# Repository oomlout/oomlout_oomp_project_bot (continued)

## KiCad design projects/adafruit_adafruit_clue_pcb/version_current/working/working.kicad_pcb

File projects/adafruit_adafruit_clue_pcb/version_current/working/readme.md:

# Adafruit-CLUE-PCB by adafruit  
This is a harvested standardized copy of a project from github.  
The original project can be found at:  
https://github.com/adafruit/Adafruit-CLUE-PCB  
Please consult that link for additional, details, files, and license information.  
Note: It was auto harvested and if the original repo had more than one board file or anything out of the ordinary the files here are likely not representative.

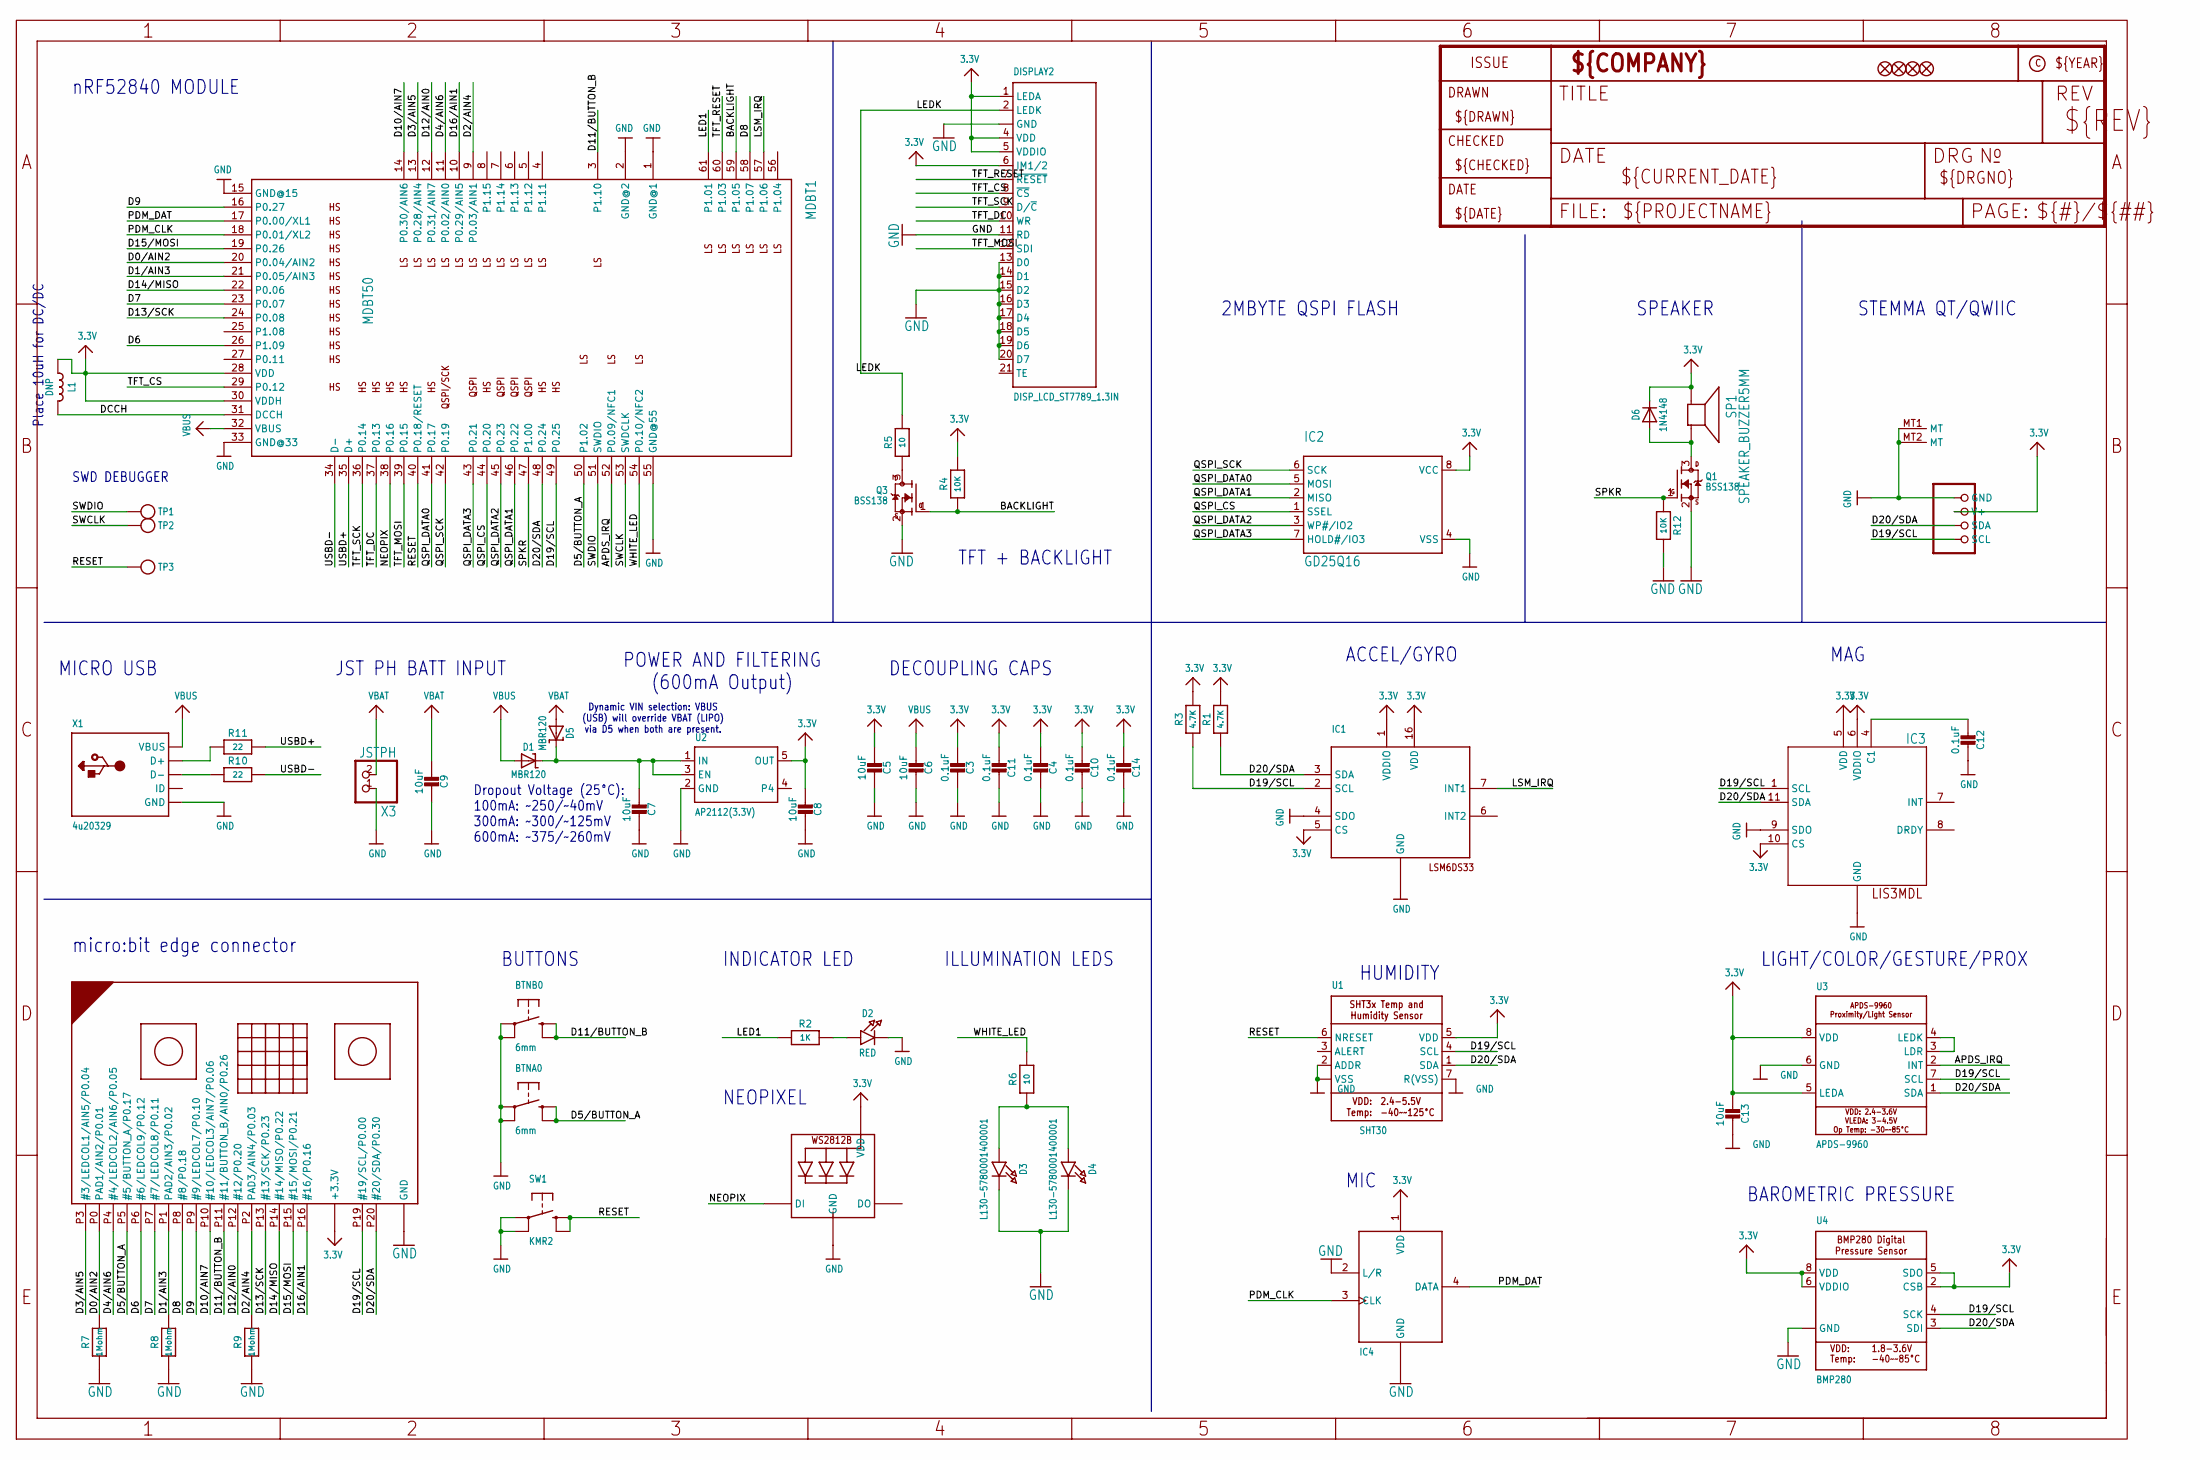
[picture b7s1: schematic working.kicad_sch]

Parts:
BTNA0: 6mm; 6MMX6MM_TACTILE_SMT
BTNB0: 6mm; 6MMX6MM_TACTILE_SMT
C3, C4, C10, C11, C12, C14: 0.1uF; 0603-NO
C5, C6, C7, C8, C9, C13: 10uF; 0805-NO
CONN1: STEMMA_I2C_QT; JST_SH4
D1, D5: MBR120; SOD-123
D2: RED; CHIPLED_0603_NOOUTLINE
D3, D4: L130-5780001400001; EVERLIGHT_45-21
D6: 1N4148; SOD-323
DISPLAY2: DISP_LCD_ST7789_1.3IN; TFT_1.3IN_240X240_24P
FID1, FID2, FID3, FID4: FIDUCIAL_1MM
IC1: LSM6DS33; LGA16_3X3MM
IC2: GD25Q16; SOIC8_150MIL
IC3: LIS3MDL; LGA12_2X2MM
IC4: MIC_PDM_SPK0415; SPK0415HM4H
L1: DNP; _0805MP
LED1: WS2812B3535; LED3535
MB1: MICRO:BIT_EDGE; MICROBIT_EDGE
MDBT1: MDBT50
Q1, Q3: BSS138; SOT23-WIDE
R1, R3: 4.7K; 0603-NO
R2: 1K; 0603-NO
R4, R12: 10K; 0603-NO
R5, R6: 10; 0603-NO
R7, R8, R9: 1Mohm; 0603-NO
R10, R11: 22; 0603-NO
SP1: SPEAKER_BUZZER5MM; BUZZER_SMT_5MM
SW1: KMR2; EVQ-Q2_SMALLER
TP1, TP2, TP3: TESTPOINTROUND1.5MM; TESTPOINT_ROUND_1.5MM
U1: SHT30; SHT3X
U2: AP2112(3.3V); SOT23-5
U3: APDS-9960
U4: BMP280
X1: 4u20329; 4UCONN_20329_SLIM
X3: JSTPH; JSTPH2

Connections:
3.3V: C3.2, C4.2, C5.2, C8.2, C10.2, C11.2, C13.2, C14.2, CONN1.2 (V+), D6.C, DISPLAY2.1 (LEDA), DISPLAY2.4 (VDD), DISPLAY2.5 (VDDIO), DISPLAY2.6 (IM1/2), IC1.1 (VDDIO), IC1.5 (CS), IC1.16 (VDD), IC2.8 (VCC), IC3.5 (VDD), IC3.6 (VDDIO), IC3.10 (CS), IC4.1 (VDD), L1.1, LED1.2 (VDD), MB1.+3V3 (+3.3V), MB1.+3V3@1 (+3.3V), MB1.+3V3@2 (+3.3V), MDBT1.28 (VDD), MDBT1.30 (VDDH), R1.2, R3.2, R4.2, SP1.+, U1.5 (VDD), U2.5 (OUT), U3.5 (LEDA), U3.8 (VDD), U4.2 (CSB), U4.5 (SDO), U4.6 (VDDIO), U4.8 (VDD)
APDS_IRQ: MDBT1.52 (P0.09/NFC1), U3.2 (INT)
BACKLIGHT: MDBT1.59 (P1.05), Q3.1 (G), R4.1
CAP1: C12.2, IC3.4 (C1)
D0/AIN2: MB1.P0 (PAD1/AIN2/P0.01), MDBT1.20 (P0.04/AIN2), R7.2
D1/AIN3: MB1.P1 (PAD2/AIN3/P0.02), MDBT1.21 (P0.05/AIN3), R8.2
D2/AIN4: MB1.P2 (PAD3/AIN4/P0.03), MDBT1.9 (P0.03/AIN1), R9.2
D3/AIN5: MB1.P3 (#3/LEDCOL1/AIN5/P0.04), MDBT1.13 (P0.28/AIN4)
D4/AIN6: MB1.P4 (#4/LEDCOL2/AIN6/P0.05), MDBT1.11 (P0.02/AIN0)
D5/BUTTON_A: BTNA0.B (S), BTNA0.B' (S1), MB1.P5 (#5/BUTTON_A/P0.17), MDBT1.50 (P1.02)
D6: MB1.P6 (#6/LEDCOL9/P0.12), MDBT1.26 (P1.09)
D7: MB1.P7 (#7/LEDCOL8/P0.11), MDBT1.23 (P0.07)
D8: MB1.P8 (#8/P0.18), MDBT1.58 (P1.07)
D9: MB1.P9 (#9/LEDCOL7/P0.10), MDBT1.16 (P0.27)
D10/AIN7: MB1.P10 (#10/LEDCOL3/AIN7/P0.06), MDBT1.14 (P0.30/AIN6)
D11/BUTTON_B: BTNB0.B (S), BTNB0.B' (S1), MB1.P11 (#11/BUTTON_B/AIN0/P0.26), MDBT1.3 (P1.10)
D12/AIN0: MB1.P12 (#12/P0.20), MDBT1.12 (P0.31/AIN7)
D13/SCK: MB1.P13 (#13/SCK/P0.23), MDBT1.24 (P0.08)
D14/MISO: MB1.P14 (#14/MISO/P0.22), MDBT1.22 (P0.06)
D15/MOSI: MB1.P15 (#15/MOSI/P0.21), MDBT1.19 (P0.26)
D16/AIN1: MB1.P16 (#16/P0.16), MDBT1.10 (P0.29/AIN5)
D19/SCL: CONN1.4 (SCL), IC1.2 (SCL), IC3.1 (SCL), MB1.P19 (#19/SCL/P0.00), MDBT1.49 (P0.25), R3.1, U1.4 (SCL), U3.7 (SCL), U4.4 (SCK)
D20/SDA: CONN1.3 (SDA), IC1.3 (SDA), IC3.11 (SDA), MB1.P20 (#20/SDA/P0.30), MDBT1.48 (P0.24), R1.1, U1.1 (SDA), U3.1 (SDA), U4.3 (SDI)
D+: R11.1, X1.D+
D-: R10.1, X1.D-
DCCH: L1.2, MDBT1.31 (DCCH)
GND: BTNA0.A, BTNA0.A' (P1), BTNB0.A, BTNB0.A' (P1), C3.1, C4.1, C5.1, C6.1, C7.1, C8.1, C9.1, C10.1, C11.1, C12.1, C13.1, C14.1, CONN1.1 (GND), CONN1.MT1 (MT), CONN1.MT2 (MT), D2.C, D3.K (C), D4.K (C), DISPLAY2.3 (GND), DISPLAY2.11 (RD), DISPLAY2.13 (D0), DISPLAY2.14 (D1), DISPLAY2.15 (D2), DISPLAY2.16 (D3), DISPLAY2.17 (D4), DISPLAY2.18 (D5), DISPLAY2.19 (D6), DISPLAY2.20 (D7), DISPLAY2.23 (GND), DISPLAY2.24 (GND), IC1.4 (SDO), IC1.8 (GND), IC1.9 (GND), IC1.10 (GND), IC1.11 (GND), IC1.12 (GND), IC1.13 (GND), IC1.15 (GND), IC2.4 (VSS), IC3.2 (GND), IC3.3 (GND), IC3.9 (SDO), IC3.12 (GND), IC4.2 (L/R), IC4.5 (GND), IC4.6 (GND), IC4.7 (GND), IC4.8 (GND), LED1.4 (GND), MB1.GND, MB1.GND@1 (GND), MB1.GND@2 (GND), MDBT1.1 (GND@1), MDBT1.2 (GND@2), MDBT1.15 (GND@15), MDBT1.33 (GND@33), MDBT1.55 (GND@55), Q1.2 (S), Q3.2 (S), R7.1, R8.1, R9.1, R12.2, SW1.A, SW1.A' (P1), U1.2 (ADDR), U1.7 (R(VSS)), U1.8 (VSS), U1.THERMAL (VSS), U2.2 (GND), U3.6 (GND), U4.1 (GND), U4.7 (GND), X1.BASE@1 (GND), X1.BASE@2 (GND), X1.GND, X1.SPRT@1 (GND), X1.SPRT@2 (GND), X1.SPRT@3 (GND), X1.SPRT@4 (GND), X3.1
LED1: MDBT1.61 (P1.01), R2.1
LEDK: DISPLAY2.2 (LEDK), R5.2
LSM_IRQ: IC1.7 (INT1), MDBT1.57 (P1.06)
unnamed: Q3.3 (D), R5.1
unnamed: U3.3 (LDR), U3.4 (LEDK)
unnamed: D3.A, D4.A, R6.1
unnamed: D6.A, Q1.3 (D), SP1.-
unnamed: D2.A, R2.2
NEOPIX: LED1.1 (DI), MDBT1.38 (P0.16)
PDM_CLK: IC4.3 (CLK), MDBT1.18 (P0.01/XL2)
PDM_DAT: IC4.4 (DATA), MDBT1.17 (P0.00/XL1)
QSPI_CS: IC2.1 (SSEL), MDBT1.44 (P0.20)
QSPI_DATA0: IC2.5 (MOSI), MDBT1.41 (P0.17)
QSPI_DATA1: IC2.2 (MISO), MDBT1.46 (P0.22)
QSPI_DATA2: IC2.3 (WP#/IO2), MDBT1.45 (P0.23)
QSPI_DATA3: IC2.7 (HOLD#/IO3), MDBT1.43 (P0.21)
QSPI_SCK: IC2.6 (SCK), MDBT1.42 (P0.19)
RESET: MDBT1.40 (P0.18/RESET), SW1.B (S), SW1.B' (S1), TP3.P$1, U1.6 (NRESET)
SPKR: MDBT1.47 (P1.00), Q1.1 (G), R12.1
SWCLK: MDBT1.53 (SWDCLK), TP2.P$1
SWDIO: MDBT1.51 (SWDIO), TP1.P$1
TFT_CS: DISPLAY2.8 (~CS), MDBT1.29 (P0.12)
TFT_DC: DISPLAY2.10 (WR), MDBT1.37 (P0.13)
TFT_MOSI: DISPLAY2.12 (SDI), MDBT1.39 (P0.15)
TFT_RESET: DISPLAY2.7 (~RESET), MDBT1.60 (P1.03)
TFT_SCK: DISPLAY2.9 (D/~C), MDBT1.36 (P0.14)
USBD+: MDBT1.35 (D+), R11.2
USBD-: MDBT1.34 (D-), R10.2
VBAT: C9.2, D5.A, X3.2
VBUS: C6.2, D1.A, MDBT1.32 (VBUS), X1.VBUS
VHI: C7.2, D1.C, D5.C, U2.1 (IN), U2.3 (EN)
WHITE_LED: MDBT1.54 (P0.10/NFC2), R6.2

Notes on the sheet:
BUTTONS
POWER AND FILTERING (600mA Output)
NEOPIXEL
TFT + BACKLIGHT
STEMMA QT/QWIIC
MICRO USB
HUMIDITY
MIC
Place 10uH for DC/DC
nRF52840 MODULE
MAG
2MBYTE QSPI FLASH
INDICATOR LED
ACCEL/GYRO
DECOUPLING CAPS
ILLUMINATION LEDS
SPEAKER
SWD DEBUGGER
BAROMETRIC PRESSURE
Dropout Voltage (25°C): 100mA: ~250/~40mV 300mA: ~300/~125mV 600mA: ~375/~260mV
LIGHT/COLOR/GESTURE/PROX
JST PH BATT INPUT
Dynamic VIN selection: VBUS (USB) will override VBAT (LIPO) via D5 when both are present.
micro:bit edge connector

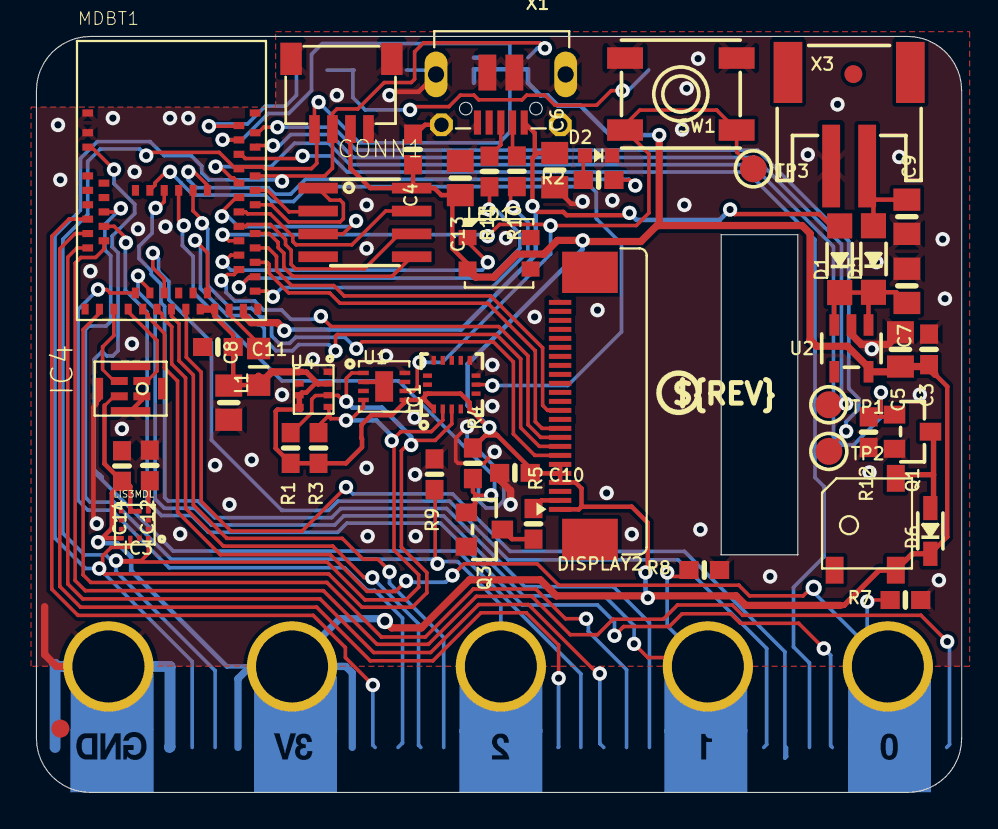
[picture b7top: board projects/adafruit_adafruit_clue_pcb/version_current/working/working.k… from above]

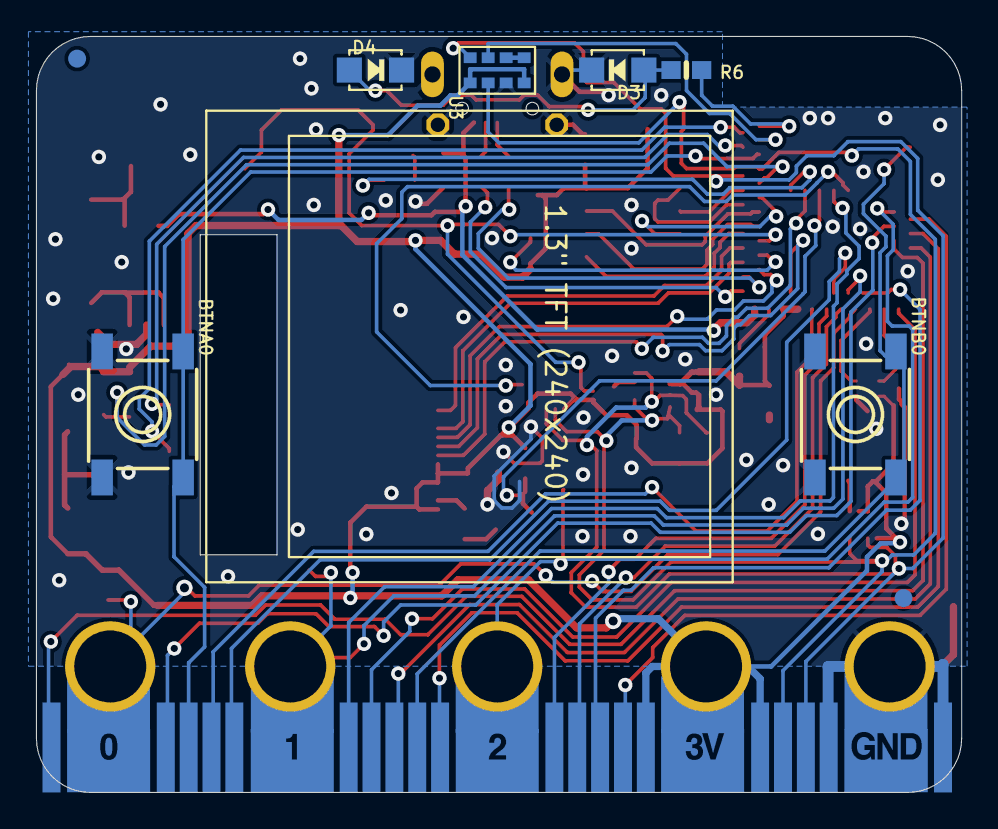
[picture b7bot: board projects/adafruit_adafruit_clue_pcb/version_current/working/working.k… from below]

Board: 2 copper layers, 51.4 x 42.0 mm, 62 parts (10 on the bottom side), 59 nets.

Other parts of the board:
U$10: PCBFEAT-REV-056
U$37: CLUE_BACK
U$52: CLUE_FRONT

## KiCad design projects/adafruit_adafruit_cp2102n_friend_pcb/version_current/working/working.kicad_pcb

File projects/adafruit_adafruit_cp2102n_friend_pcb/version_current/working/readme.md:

# Adafruit-CP2102N-Friend-PCB by adafruit  
This is a harvested standardized copy of a project from github.  
The original project can be found at:  
https://github.com/adafruit/Adafruit-CP2102N-Friend-PCB  
Please consult that link for additional, details, files, and license information.  
Note: It was auto harvested and if the original repo had more than one board file or anything out of the ordinary the files here are likely not representative.

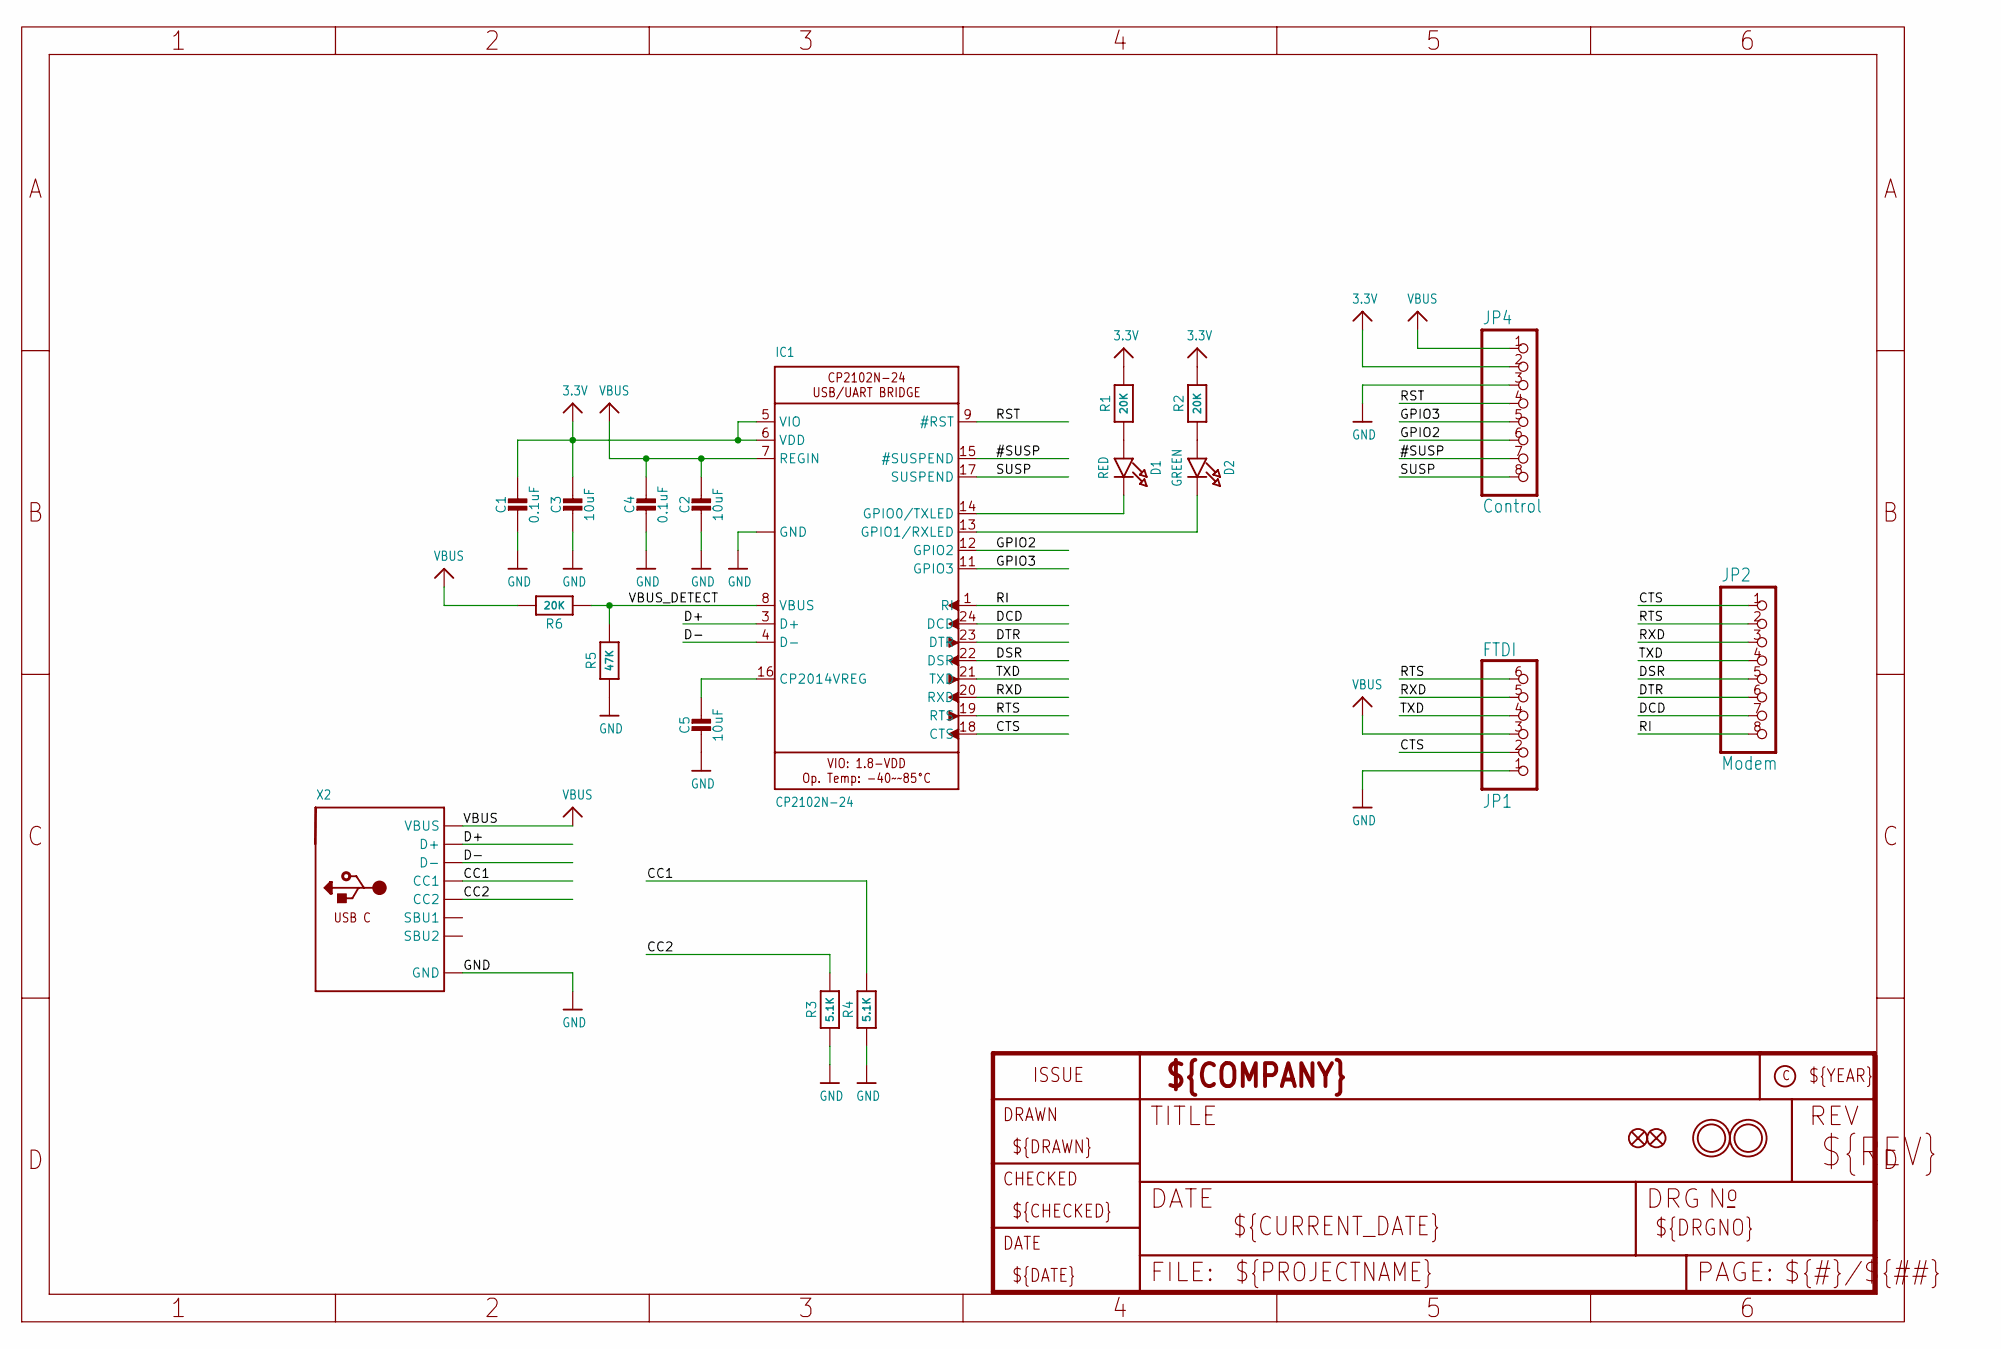
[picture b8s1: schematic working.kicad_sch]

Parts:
C1, C4: 0.1uF; 0603-NO
C2, C3, C5: 10uF; 0805-NO
D1: RED; CHIPLED_0603_NOOUTLINE
D2: GREEN; CHIPLED_0603_NOOUTLINE
FID1, FID2: FIDUCIAL_1MM
IC1: CP2102N-24; QFN24_4MM_SMSC
JP1: FTDI; 1X06_ROUND_76
JP2: Modem; 1X08_ROUND_70
JP4: Control; 1X08_ROUND_70
R1, R2, R6: 20K; 0603-NO
R3, R4: 5.1K; 0603-NO
R5: 47K; 0603-NO
U$18, U$19: MOUNTINGHOLE2.0; MOUNTINGHOLE_2.0_PLATED
X2: USB_C; USB_C_CUSB31-CFM2AX-01-X

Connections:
3.3V: C1.1, C3.1, IC1.5 (VIO), IC1.6 (VDD), JP4.2, R1.2, R2.2
#SUSP: IC1.15 (#SUSPEND), JP4.7
CC1: R4.2, X2.A5 (CC1)
CC2: R3.2, X2.B5 (CC2)
CTS: IC1.18 (CTS), JP1.2, JP2.1
D+: IC1.3 (D+), X2.A6 (D+), X2.B6 (D+)
D-: IC1.4 (D-), X2.A7 (D-), X2.B7 (D-)
DCD: IC1.24 (DCD), JP2.7
DSR: IC1.22 (DSR), JP2.5
DTR: IC1.23 (DTR), JP2.6
GND: C1.2, C2.2, C3.2, C4.2, C5.2, IC1.2 (GND), IC1.THERM (GND), JP1.1, JP4.3, R3.1, R4.1, R5.1, X2.A1B12 (GND), X2.B1A12 (GND)
GPIO2: IC1.12 (GPIO2), JP4.6
GPIO3: IC1.11 (GPIO3), JP4.5
unnamed: D1.A, R1.1
unnamed: C5.1, IC1.16 (CP2014VREG)
unnamed: D2.A, R2.1
unnamed: D1.C, IC1.14 (GPIO0/TXLED)
unnamed: D2.C, IC1.13 (GPIO1/RXLED)
RI: IC1.1 (RI), JP2.8
RST: IC1.9 (#RST), JP4.4
RTS: IC1.19 (RTS), JP1.6, JP2.2
RXD: IC1.20 (RXD), JP1.5, JP2.3
SUSP: IC1.17 (SUSPEND), JP4.8
TXD: IC1.21 (TXD), JP1.4, JP2.4
VBUS: C2.1, C4.1, IC1.7 (REGIN), JP1.3, JP4.1, R6.2, X2.A4B9 (VBUS), X2.B4A9 (VBUS)
VBUS_DETECT: IC1.8 (VBUS), R5.2, R6.1

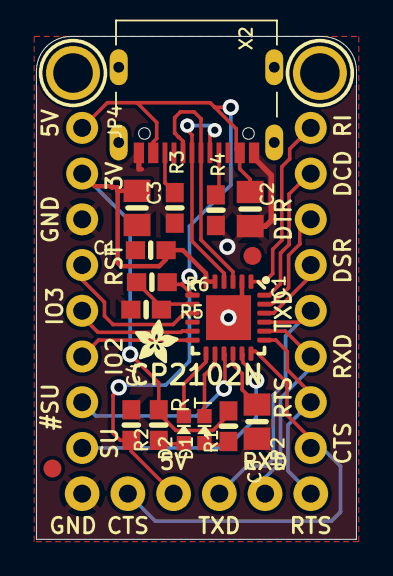
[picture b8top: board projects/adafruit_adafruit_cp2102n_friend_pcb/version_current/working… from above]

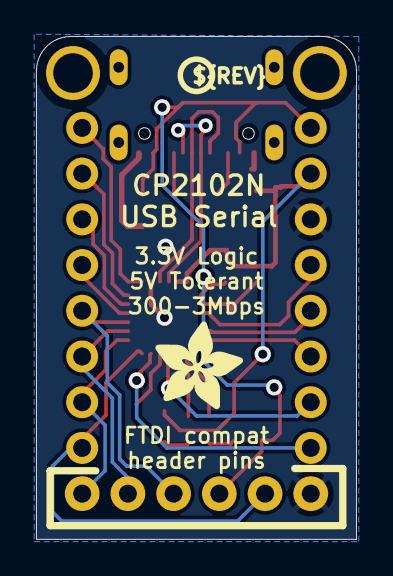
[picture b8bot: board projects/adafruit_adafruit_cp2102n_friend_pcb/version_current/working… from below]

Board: 2 copper layers, 17.8 x 27.9 mm, 25 parts (2 on the bottom side), 26 nets.

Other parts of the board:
U$8: ADAFRUIT_2.5MM
U$17: PCBFEAT-REV-040
U$22: ADAFRUIT_5MM
